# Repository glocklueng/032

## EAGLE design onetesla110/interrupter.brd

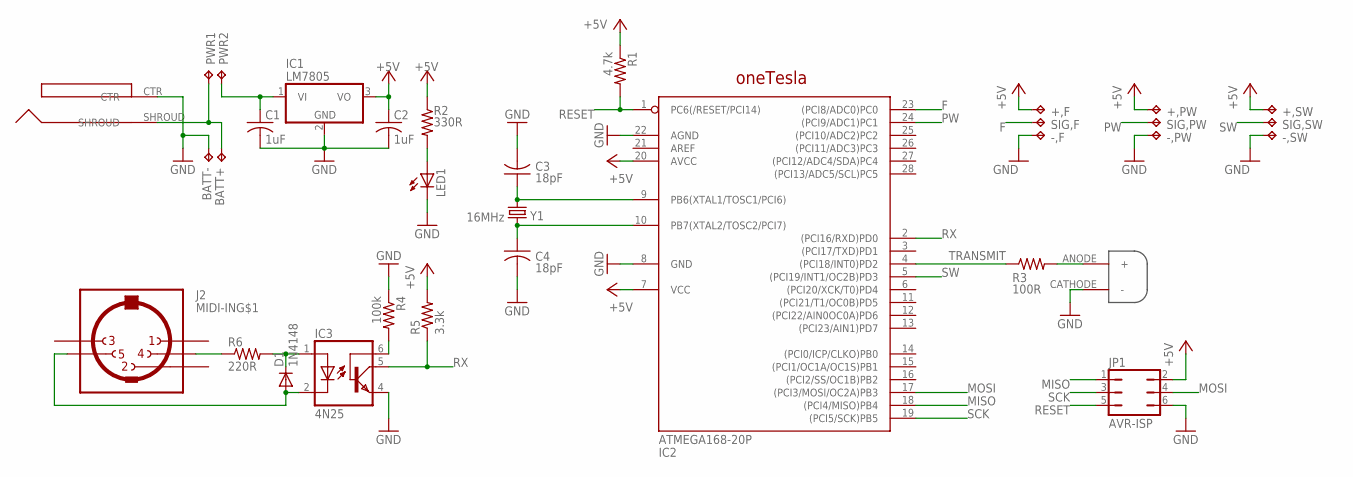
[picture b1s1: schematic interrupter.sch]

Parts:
+,F: TPPAD1-13; P1-13
+,PW: TPPAD1-13; P1-13
+,SW: TPPAD1-13; P1-13
-,F: TPPAD1-13; P1-13
-,PW: TPPAD1-13; P1-13
-,SW: TPPAD1-13; P1-13
BATT+: TPPAD1-13; P1-13
BATT-: TPPAD1-13; P1-13
C1, C2: 1uF; C050-024X044
C3, C4: 18pF; C025-024X044
D1: 1N4148; DO35-7
IC1: LM7805; TO220H
IC2: ATMEGA168-20P; DIL28-3
IC3: 4N25; DIL06
JP1: AVR-ISP; JP3Q
LED1: LED5MM
MIDI-IN: J2; CP-2350
POWER: J1; DJC0202
PWR1, PWR2: TPPAD1-13; P1-13
R1: 4.7k; 0207/7
R2: 330R; 0207/7
R3: 100R; 0207/7
R4: 100k; 0207/7
R5: 3.3k; 0207/7
R6: 220R; 0207/7
SIG,F: TPPAD1-13; P1-13
SIG,PW: TPPAD1-13; P1-13
SIG,SW: TPPAD1-13; P1-13
U$1: LOGO
U$2: IFE96_OPTO; IFE96
Y1: 16MHz; HC49U-V

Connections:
+5V: +,F.TP, +,PW.TP, +,SW.TP, C2.1, IC1.3 (VO), IC2.7 (VCC), IC2.20 (AVCC), JP1.2, R1.1, R2.1, R5.2
F: IC2.23 ((PCI8/ADC0)PC0), SIG,F.TP
GND: -,F.TP, -,PW.TP, -,SW.TP, BATT-.TP, C1.2, C2.2, C3.2, C4.2, IC1.2 (GND), IC2.8 (GND), IC2.22 (AGND), IC3.4 (EMI), JP1.6, LED1.K (C), POWER.CTR, R4.1, U$2.CATHODE (-)
MISO: IC2.18 ((PCI4/MISO)PB4), JP1.1
MOSI: IC2.17 ((PCI3/MOSI/OC2A)PB3), JP1.4
unnamed: D1.C, IC3.1 (A), R6.2
unnamed: D1.A, IC3.2 (C), MIDI-IN.5
unnamed: IC3.6 (BAS), R4.2
unnamed: C3.1, IC2.9 (PB6(XTAL1/TOSC1/PCI6)), Y1.2
unnamed: C1.1, IC1.1 (VI), PWR2.TP
unnamed: MIDI-IN.4, R6.1
unnamed: C4.1, IC2.10 (PB7(XTAL2/TOSC2/PCI7)), Y1.1
unnamed: R3.2, U$2.ANODE (+)
unnamed: LED1.A, R2.2
unnamed: BATT+.TP, POWER.SHROUD, PWR1.TP
PW: IC2.24 ((PCI9/ADC1)PC1), SIG,PW.TP
RESET: IC2.1 (PC6(/RESET/PCI14)), JP1.5, R1.2
RX: IC2.2 ((PCI16/RXD)PD0), IC3.5 (COL), R5.1
SCK: IC2.19 ((PCI5/SCK)PB5), JP1.3
SW: IC2.5 ((PCI19/INT1/OC2B)PD3), SIG,SW.TP
TRANSMIT: IC2.4 ((PCI18/INT0)PD2), R3.1

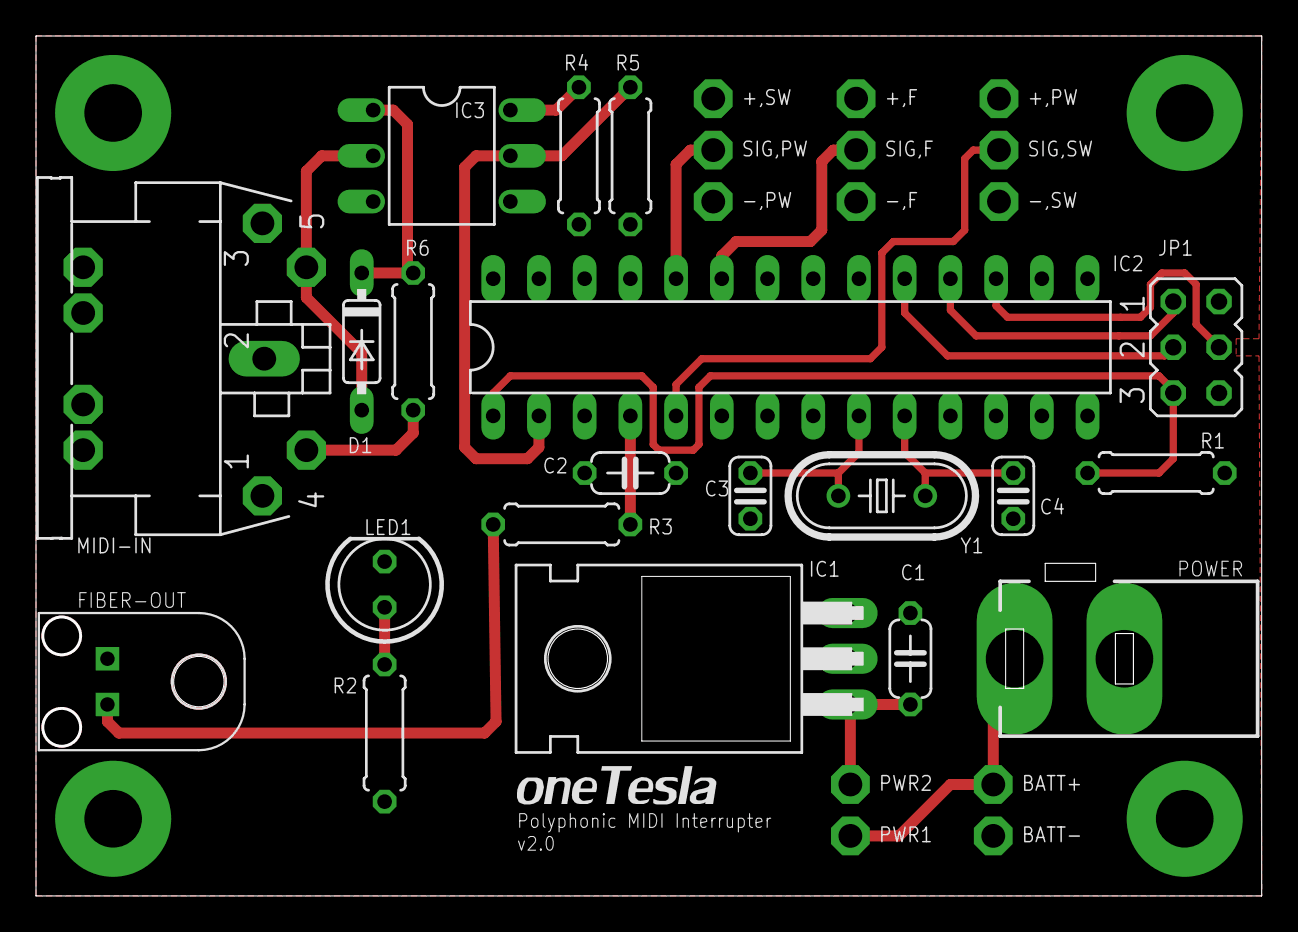
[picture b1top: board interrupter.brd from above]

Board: 2 copper layers, 68.1 x 47.8 mm, 34 parts (0 on the bottom side), 21 nets.

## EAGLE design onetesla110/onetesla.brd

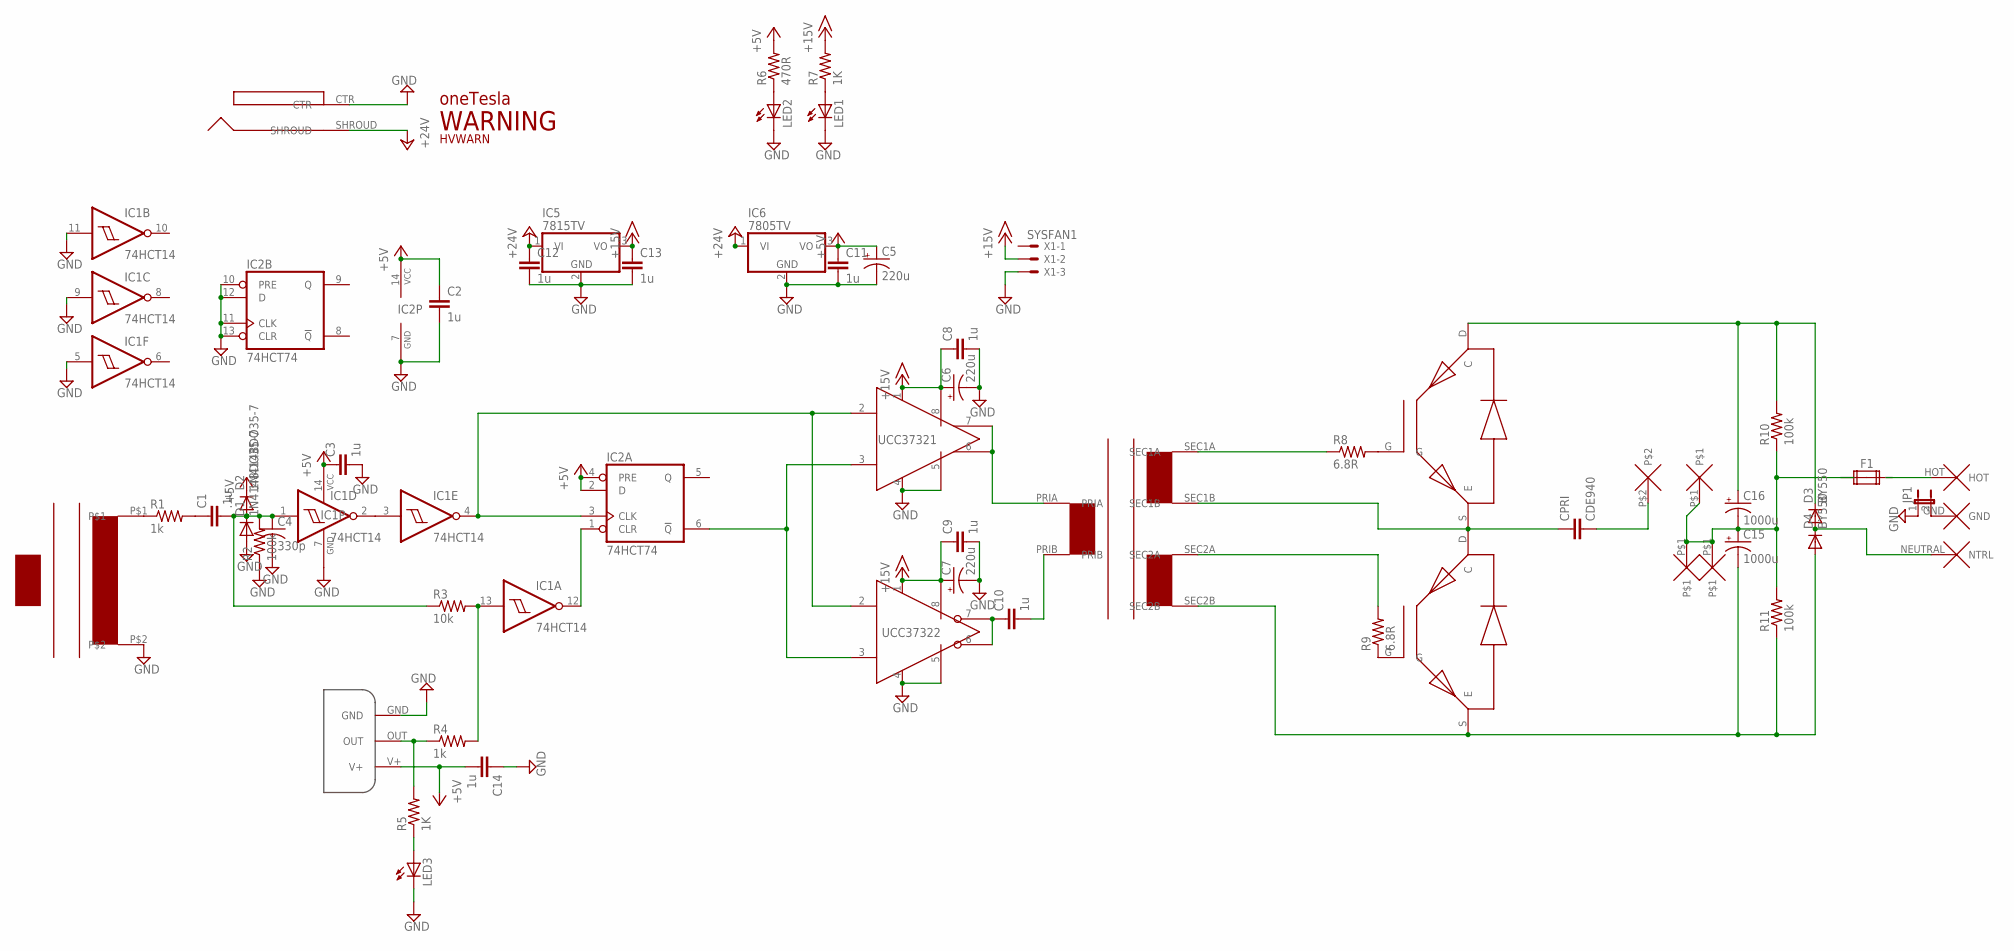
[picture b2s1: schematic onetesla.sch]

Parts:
C1: .1u; C050-024X044
C2, C3, C8, C9, C10, C11, C12, C13, C14: 1u; C050-024X044
C4: 330p; C025-024X044
C5, C6, C7: 220u; E5-10,5
C15, C16: 1000u; EB25D
CPRI: CDE940
CT1: TRIAD_CT; CT2
D1, D2: 1N4148DO35-7; DO35-7
D3, D4: BY550; DO27-15
F1: FUSE2P; FUSE1
FB1: IFD95_OPTO; IFD95
IC1: 74HCT14; DIL14
IC2: 74HCT74; DIL14
IC3: UCC37321DIL8; DIL08
IC4: UCC37322DIL8; DIL08
IC5: 7815TV; TO220V
IC6: 7805TV; TO220V
J1: DC-IN; DJC0202
J2: IEC; IECPORT
JP1: JP1E; JP1
LED1, LED2, LED3: LED5MM
LPRI: 2TERMINAL
Q1, Q2: FGA60N65SMD; TO247BV
R1: 1k; 0922/22
R2: 100k; 0204/7
R3: 10k; 0204/7
R4: 1k; 0204/7
R5, R7: 1K; 0207/7
R6: 470R; 0207/7
R8, R9: 6.8R; 0309V
R10, R11: 100k; 0309/10
U$1: LOGO
U$2: GDT
U$3: WARNING
U$4: HVWARNING
U$9, U$11: 12AWG_PAD
X1: SYSFAN1; 22-23-2031

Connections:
+5V: C2.1, C3.1, C5.+, C11.1, C14.2, D2.C, FB1.V+, IC1.14 (VCC), IC2.2 (D), IC2.4 (PRE), IC2.14 (VCC), IC6.3 (VO), R6.2
+15V: C6.+, C7.+, C8.1, C9.1, C13.1, IC3.1 (1_VDD), IC3.8 (8_VDD), IC4.1 (1_VDD), IC4.8 (8_VDD), IC5.3 (VO), R7.2, X1.2
+24V: C12.1, IC5.1 (VI), IC6.1 (VI), J1.SHROUD
GND: C2.2, C3.2, C4.2, C5.-, C6.-, C7.-, C8.2, C9.2, C11.2, C12.2, C13.2, C14.1, CT1.P$2, D1.A, FB1.GND, IC1.5 (I), IC1.7 (GND), IC1.9 (I), IC1.11 (I), IC2.7 (GND), IC2.10 (PRE), IC2.11 (CLK), IC2.12 (D), IC2.13 (CLR), IC3.4 (4_AGND), IC3.5 (5_PGND), IC4.4 (4_AGND), IC4.5 (5_PGND), IC5.2 (GND), IC6.2 (GND), J1.CTR, JP1.1, LED1.K (C), LED2.K (C), LED3.K (C), R2.1, X1.3
unnamed: CT1.P$1, R1.1
unnamed: C1.1, R1.2
unnamed: C1.2, C4.1, D1.C, D2.A, IC1.1 (I), R2.2, R3.1
unnamed: IC1.2 (O), IC1.3 (I)
unnamed: IC2.6 (!Q), IC3.3 (3_ENBL), IC4.3 (3_ENBL)
unnamed: IC1.4 (O), IC2.3 (CLK), IC3.2 (2_IN), IC4.2 (2_IN)
unnamed: LED2.A, R6.1
unnamed: C10.2, U$2.PRIB
unnamed: CPRI.P$1 (1), Q1.S (E), Q2.D (C), U$2.SEC1B
unnamed: C10.1, IC4.6 (6_OUT), IC4.7 (7_OUT)
unnamed: IC3.6 (6_OUT), IC3.7 (7_OUT), U$2.PRIA
unnamed: Q1.G, R8.2
unnamed: LED1.A, R7.1
unnamed: Q2.G, R9.1
unnamed: FB1.OUT, R4.1, R5.2
unnamed: IC1.13 (I), R3.2, R4.2
unnamed: D3.A, D4.C, J2.NEUTRAL (NTRL)
unnamed: R8.1, U$2.SEC1A
unnamed: R9.2, U$2.SEC2A
unnamed: IC1.12 (O), IC2.1 (CLR)
unnamed: J2.GND, JP1.2
unnamed: CPRI.P$2 (2), LPRI.P$2
unnamed: F1.2A, J2.HOT
unnamed: LED3.A, R5.1
unnamed: C15.+, C16.-, F1.1A, F1.1B, LPRI.P$1, R10.1, R11.2, U$9.P$1, U$11.P$1
V+: C16.+, D3.C, Q1.D (C), R10.2
V-: C15.-, D4.A, Q2.S (E), R11.1, U$2.SEC2B

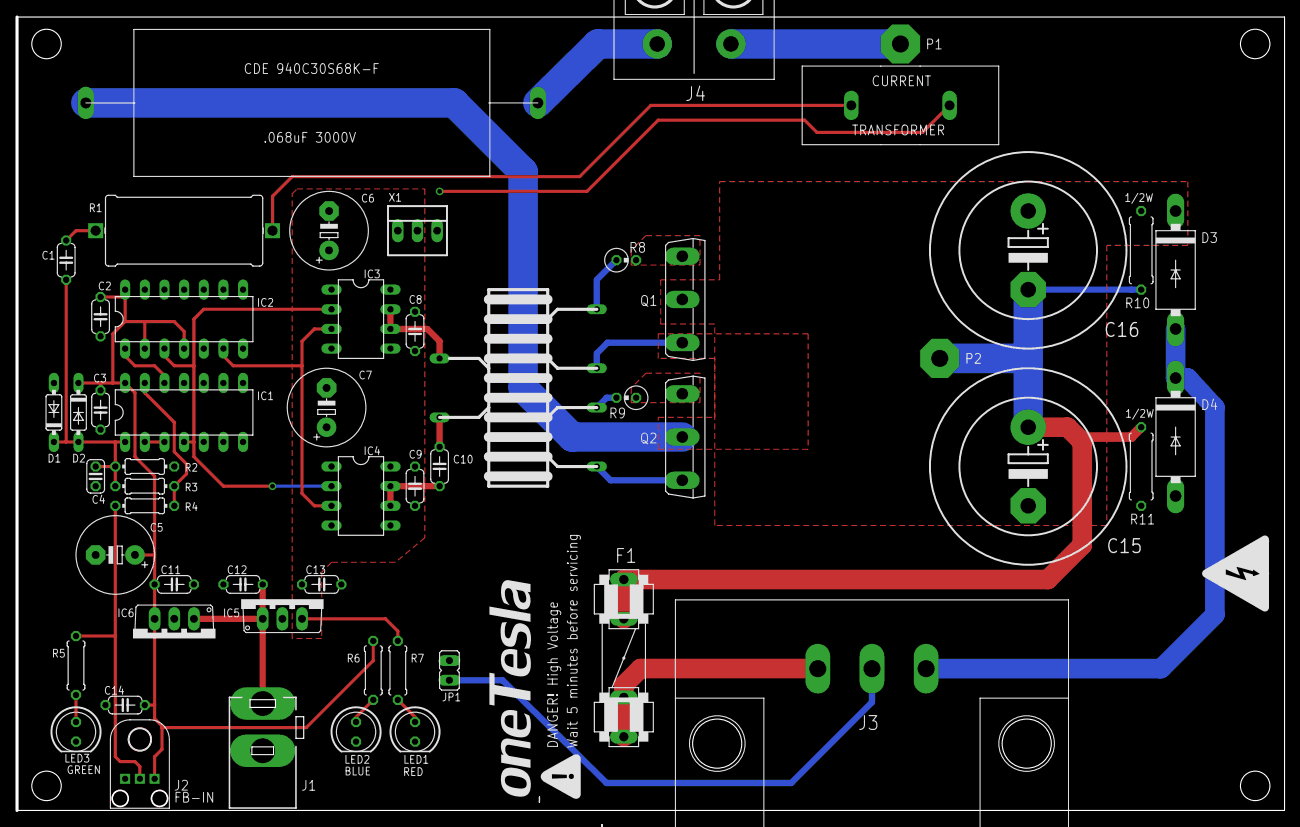
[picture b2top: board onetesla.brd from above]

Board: 3 copper layers, 163.8 x 102.5 mm, 57 parts (0 on the bottom side), 31 nets.

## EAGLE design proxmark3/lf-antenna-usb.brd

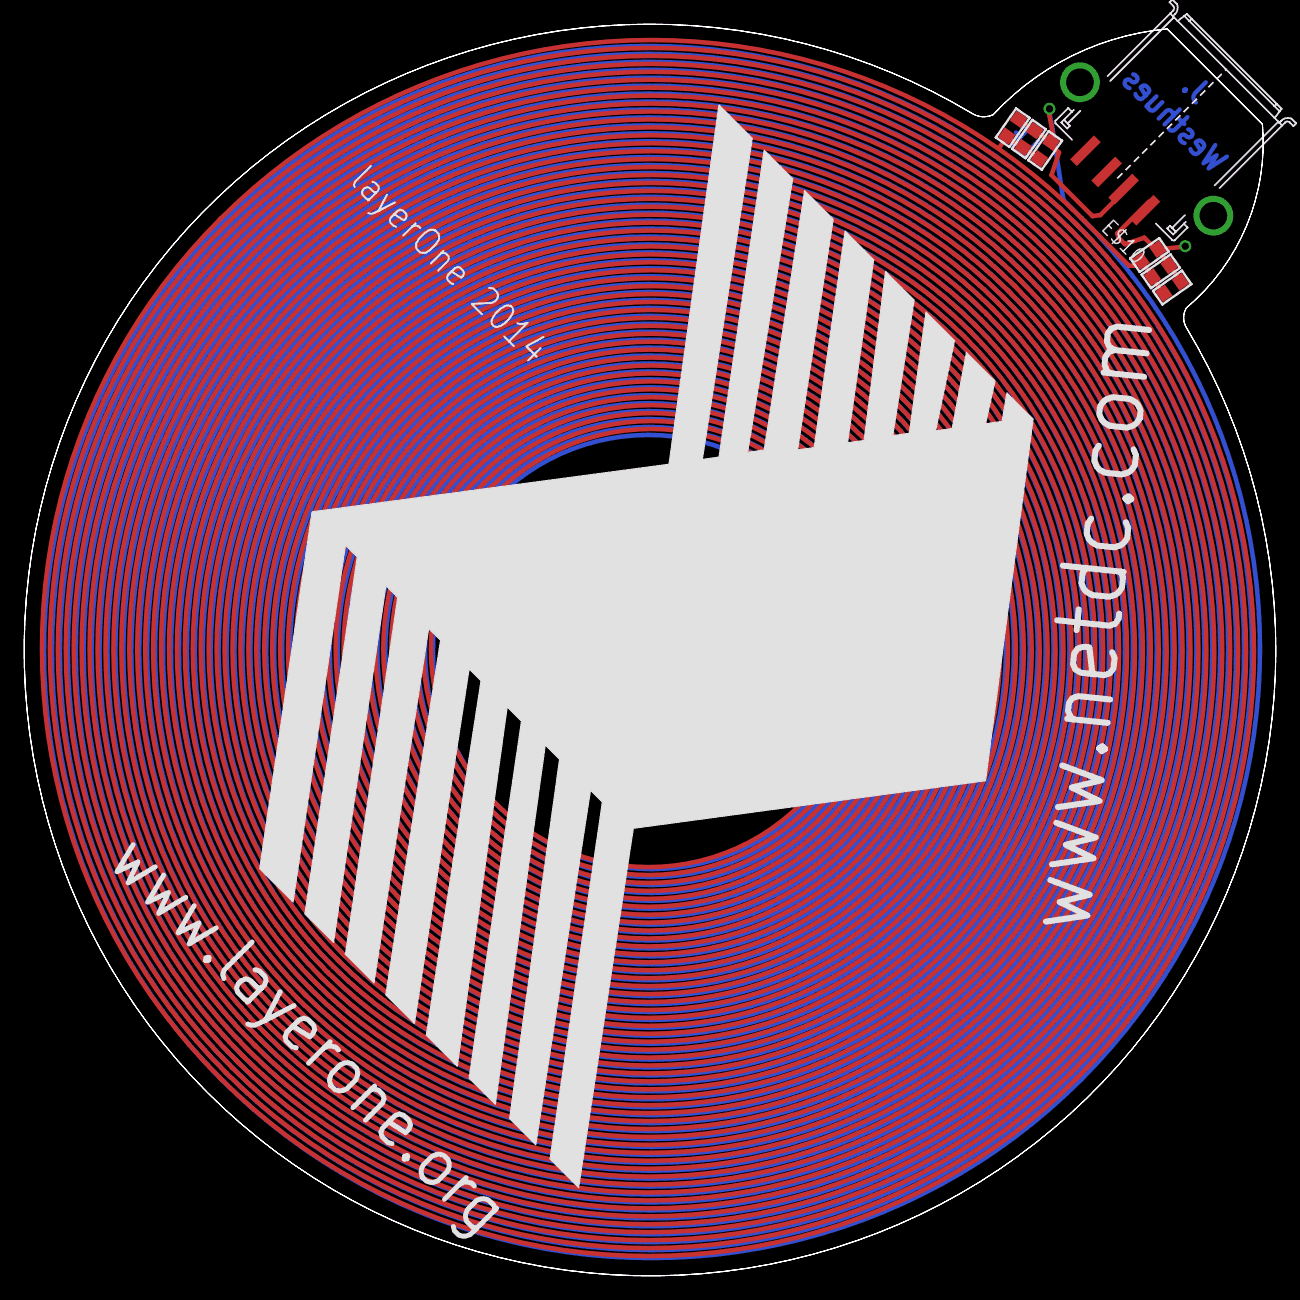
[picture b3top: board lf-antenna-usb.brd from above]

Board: 2 copper layers, 104.1 x 104.1 mm, 9 parts (0 on the bottom side), 2 nets.

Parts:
E$1, E$8: L1LOGO
E$2, E$5, E$6: dnp; RLC_0603
E$3: 1000 pF; RLC_0603
E$4: 220 pF; RLC_0603
E$7: zerohm; RLC_0603
E$10: CONN_USB_A_F

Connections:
BUFD: E$5.1, E$6.1, E$7.1
RAW: E$2.1, E$2.2, E$3.1, E$3.2, E$4.1, E$4.2, E$5.2, E$6.2, E$7.2

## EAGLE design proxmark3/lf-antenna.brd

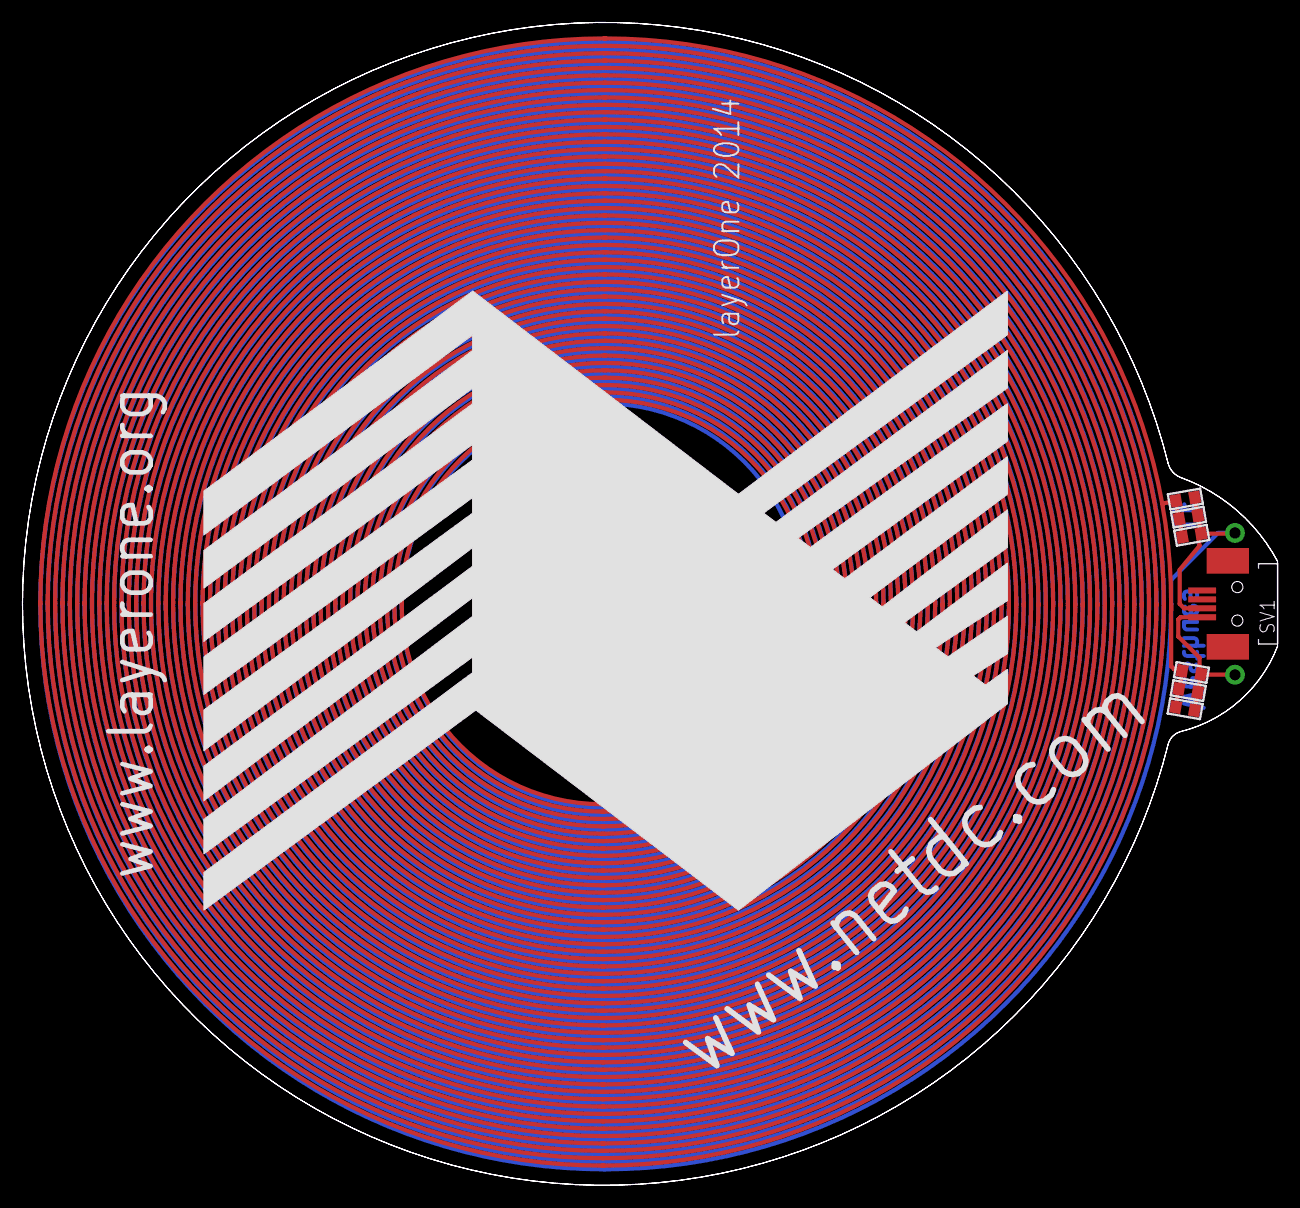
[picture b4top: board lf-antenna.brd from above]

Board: 2 copper layers, 112.4 x 104.1 mm, 9 parts (0 on the bottom side), 2 nets.

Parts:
E$1, E$8: L1LOGO
E$2, E$5, E$6: dnp; RLC_0603
E$3: 1000 pF; RLC_0603
E$4: 220 pF; RLC_0603
E$7: zerohm; RLC_0603
SV1: HIROSE-MQ172-4POS

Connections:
BUFD: E$5.1, E$6.1, E$7.1, SV1.1
RAW: E$2.1, E$2.2, E$3.1, E$3.2, E$4.1, E$4.2, E$5.2, E$6.2, E$7.2, SV1.2
